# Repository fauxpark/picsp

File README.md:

# PiCSP
The PiCSP is a very simple adapter for the Raspberry Pi that allows you to use a standard 6- or 10-pin IDC cable to program your AVR project.

It should "just work" with the avrdude package offered by the stock Raspbian repositories -- it comes with the linuxgpio programmer enabled.
The Adafruit package will probably work also, but the pinout may not be the same.

The PiCSP has two ISP headers that are electrically connected to each other, so you cannot use both at once to program two AVRs.
If you do so, you may get unexpected behaviour from avrdude, your microcontroller or your Pi!

## Pinout
The PiCSP follows the default pinout in /usr/local/etc/avrdude.conf. Make sure the pinout looks like this in your config file under the linuxgpio programmer (you may need to uncomment it before use):

| Header Pin | GPIO |
| ----------:|:---- |
| RST        |   12 |
| MISO       |   18 |
| MOSI       |   23 |
| SCK        |   24 |

This information is also printed on the PCB silkscreen, just in case.

## Assembly
Aside from the PCB itself, you will only need a 2.54mm pitch 2x20 pin socket strip, 2x3 and 2x5 pin angled IDC headers, and matching IDC ribbon cables.

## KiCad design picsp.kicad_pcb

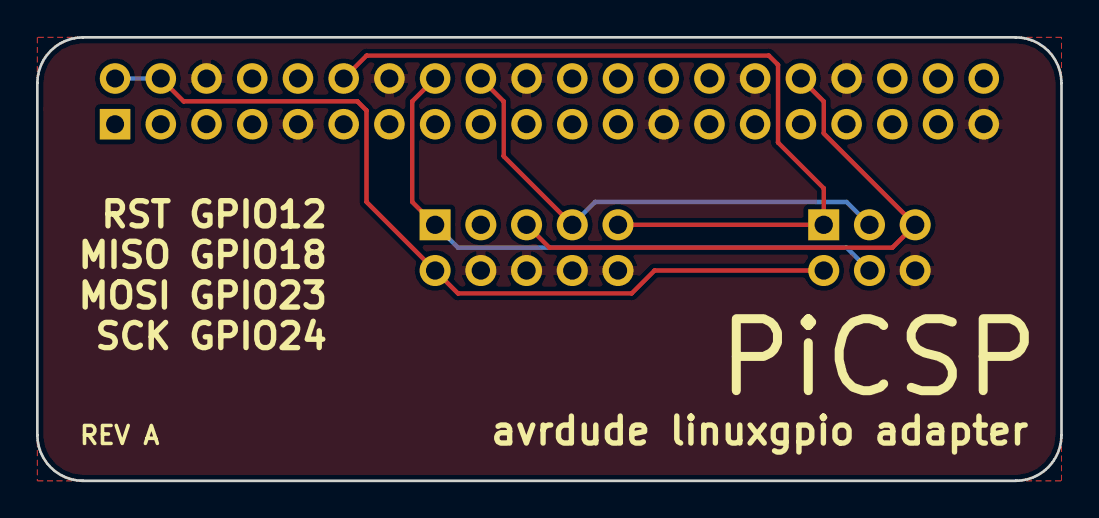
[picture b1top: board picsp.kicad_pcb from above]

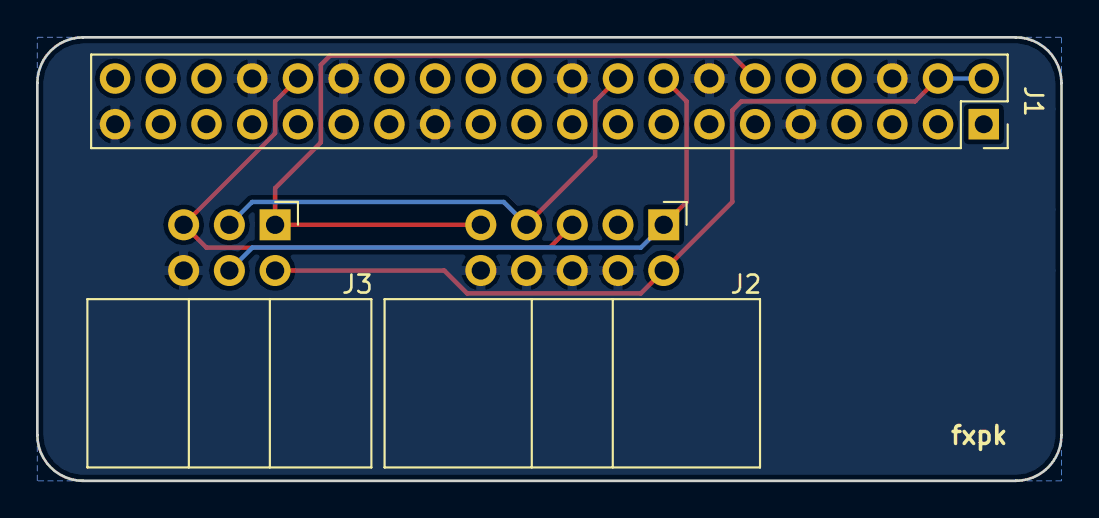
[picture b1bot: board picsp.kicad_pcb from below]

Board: 2 copper layers, 56.9 x 24.6 mm, 3 parts (3 on the bottom side), 6 nets.

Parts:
J1: Raspberry_Pi_2_3; PinSocket_2x20_P2.54mm_Vertical
J2: AVR-ISP-10; IDC-Header_2x05_P2.54mm_Horizontal
J3: AVR-ISP-6; IDC-Header_2x03_P2.54mm_Horizontal

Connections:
/MISO: J1.12, J2.9, J3.1
/MOSI: J1.16, J2.1, J3.4
/RST: J1.32, J2.5, J3.5
/SCK: J1.18, J2.7, J3.3
GND: J1.6, J1.9, J1.14, J1.20, J1.25, J1.30, J1.34, J1.39, J2.4, J2.6, J2.8, J2.10, J3.6
VCC: J1.2, J1.4, J2.2, J3.2

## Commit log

2017-10-31 Replace AVR-ISP symbols with generic 2.54mm headers
2017-10-31 Add 3D viewer images for readme
2017-10-31 Add readme
2017-11-03 Nudge the PCB slightly to align to 1.27mm grid
2018-02-27 Update project to 5.0 RC1
2018-04-15 Remove old libs from project file
2018-04-29 Update to use new library symbols
